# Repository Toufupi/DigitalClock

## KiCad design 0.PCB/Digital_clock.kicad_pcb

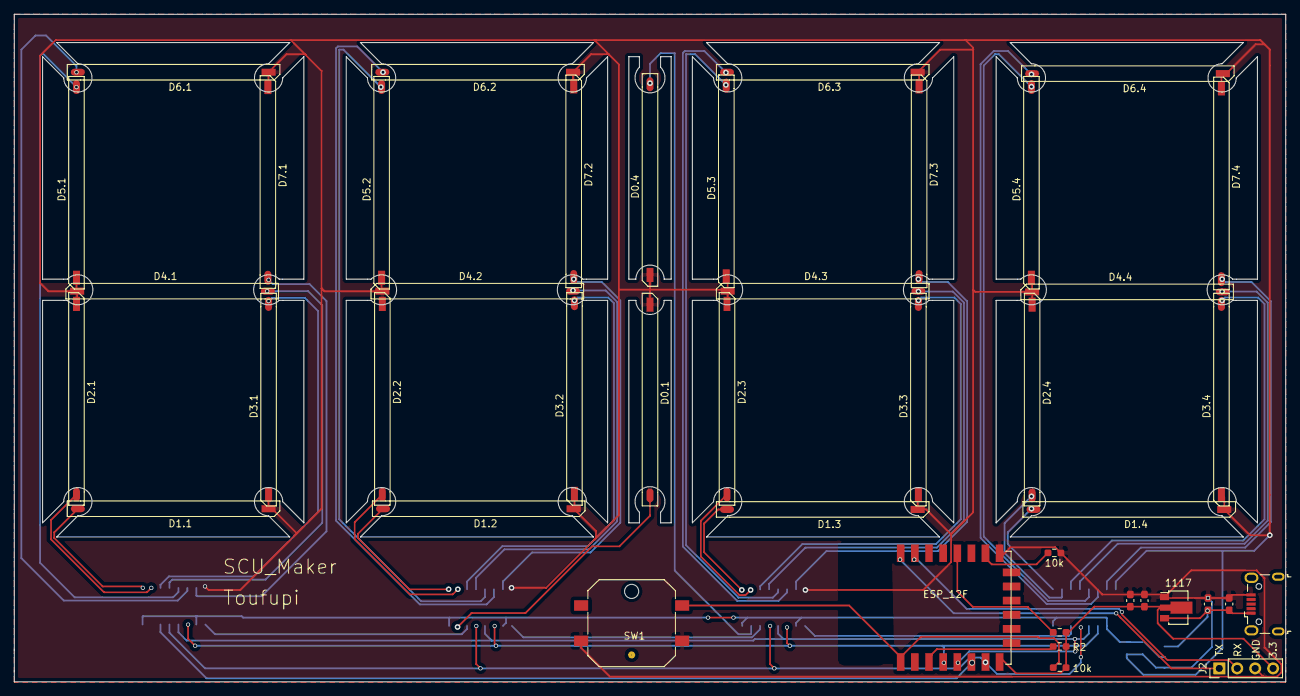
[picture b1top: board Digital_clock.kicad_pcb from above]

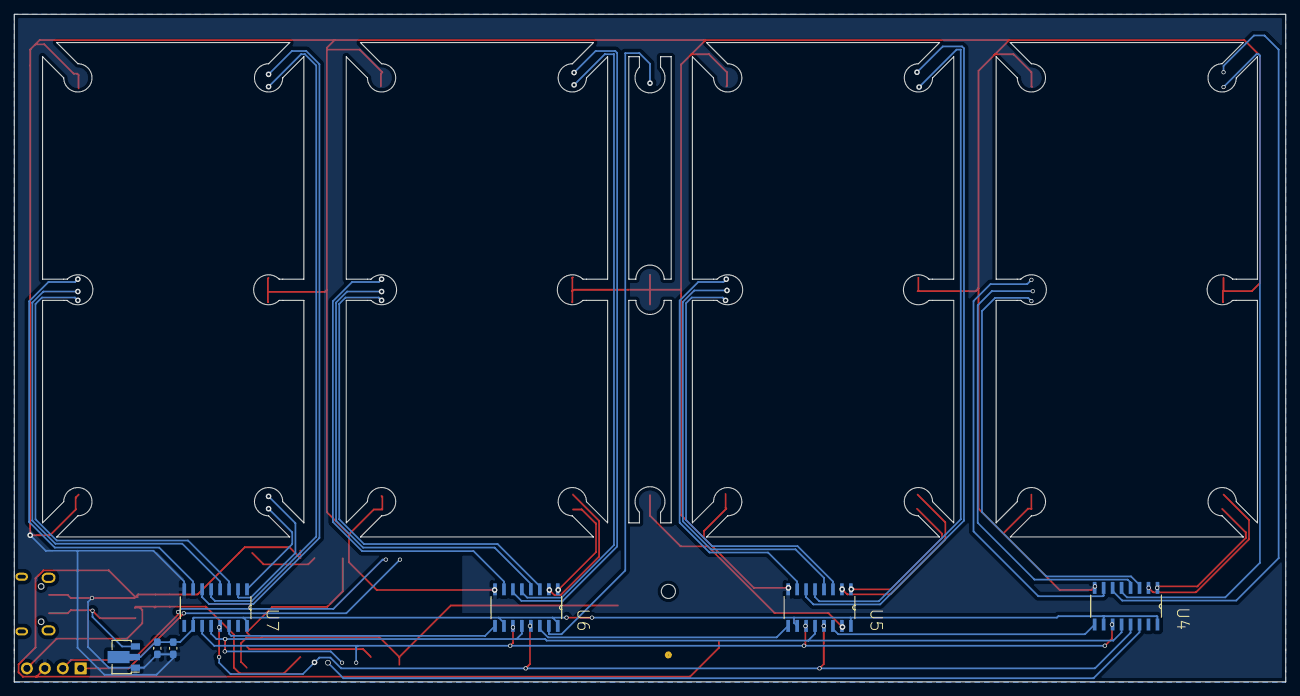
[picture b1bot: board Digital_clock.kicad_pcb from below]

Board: 2 copper layers, 180.0 x 94.5 mm, 50 parts (7 on the bottom side), 47 nets.

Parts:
10k, 10k#2: 10k; R_0603_1608Metric_Pad0.98x0.95mm_HandSolder
1117: AZ1117-3.3; SOT-89-3
C1, C4, C6: 10uf; C_0603_1608Metric_Pad1.08x0.95mm_HandSolder
C2, C3, C5: 0.1uf; C_0603_1608Metric_Pad1.08x0.95mm_HandSolder
D0.1, D0.4, D1.1, D1.2, D1.3, D1.4, D2.1, D2.2, D2.3, D2.4, D3.1, D3.2, D3.3, D3.4, D4.1, D4.2, D4.3, D4.4, D5.1, D5.2, D5.3, D5.4, D6.1, D6.2, D6.3, D6.4, D7.1, D7.2, D7.3, D7.4: LED; led_26mm
ESP_12F: ESP-12F; ESP-12E_SMD
J1: USB_B_Micro; USB_Micro-B_Wuerth_629105150521
J2: Conn_01x04; PinHeader_1x04_P2.54mm_Vertical
R2, R3: 10k; R_0603_1608Metric_Pad0.98x0.95mm_HandSolder
SW1: SW_DIP_x01; SW_Push_1P1T_NO_CK_PTS125Sx43PSMTR
U2: AZ1117-3.3; SOT-89-3
U4, U5, U6, U7: 74HC595D,118; SOIC127P600X175-16N

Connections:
/5v: 1117.3, C1.1, C2.1, J1.1, U2.3
/DS: ESP_12F.6, U4.14
/GND: 10k.1, 1117.1, C1.2, C2.2, C3.2, C4.2, C5.2, C6.2, D0.1.1, D0.4.1, D1.1.1, D1.2.1, D1.3.1, D1.4.1, D2.1.1, D2.2.1, D2.3.1, D2.4.1, D3.1.1, D3.2.1, D3.3.1, D3.4.1, D4.1.1, D4.2.1, D4.3.1, D4.4.1, D5.1.1, D5.2.1, D5.3.1, D5.4.1, D6.1.1, D6.2.1, D6.3.1, D6.4.1, D7.1.1, D7.2.1, D7.3.1, D7.4.1, ESP_12F.9, J1.5, J2.3, SW1.2, U2.1, U4.8, U5.8, U6.8, U7.8
/OE: ESP_12F.7, U4.13, U5.13, U6.13, U7.13
/SH_CP: ESP_12F.4, U4.11, U5.11, U6.11, U7.11
/ST_CP: ESP_12F.5, U4.12, U5.12, U6.12, U7.12
unnamed: C3.1, C4.1, U2.2, U4.10, U4.16, U5.10, U5.16, U6.10, U6.16, U7.10, U7.16
unnamed: 10k#2.2, 1117.2, C5.1, C6.1, ESP_12F.8, J2.4, R2.2, R3.1
unnamed: D0.1.2, U5.15
unnamed: D0.4.2, U6.15
unnamed: D1.1.2, U4.1
unnamed: D1.2.2, U5.1
unnamed: D1.3.2, U6.1
unnamed: D1.4.2, U7.1
unnamed: D2.1.2, U4.2
unnamed: D2.2.2, U5.2
unnamed: D2.3.2, U6.2
unnamed: D2.4.2, U7.2
unnamed: D3.1.2, U4.3
unnamed: D3.2.2, U5.3
unnamed: D3.3.2, U6.3
unnamed: D3.4.2, U7.3
unnamed: D4.1.2, U4.4
unnamed: D4.2.2, U5.4
unnamed: D4.3.2, U6.4
unnamed: D4.4.2, U7.4
unnamed: D5.1.2, U4.5
unnamed: D5.2.2, U5.5
unnamed: D5.3.2, U6.5
unnamed: D5.4.2, U7.5
unnamed: D6.1.2, U4.6
unnamed: D6.2.2, U5.6
unnamed: D6.3.2, U6.6
unnamed: D6.4.2, U7.6
unnamed: D7.1.2, U4.7
unnamed: D7.2.2, U5.7
unnamed: D7.3.2, U6.7
unnamed: D7.4.2, U7.7
unnamed: ESP_12F.16, J2.1
unnamed: ESP_12F.15, J2.2
unnamed: 10k#2.1, ESP_12F.1, SW1.1
unnamed: ESP_12F.3, R2.1
unnamed: ESP_12F.12, R3.2
unnamed: 10k.2, ESP_12F.10
unnamed: U4.9, U5.14
unnamed: U5.9, U6.14
unnamed: U6.9, U7.14

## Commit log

2021-02-23 set the filelibrary
2021-02-23 add pcb and sourcecode
2021-02-25 add wifi connect
